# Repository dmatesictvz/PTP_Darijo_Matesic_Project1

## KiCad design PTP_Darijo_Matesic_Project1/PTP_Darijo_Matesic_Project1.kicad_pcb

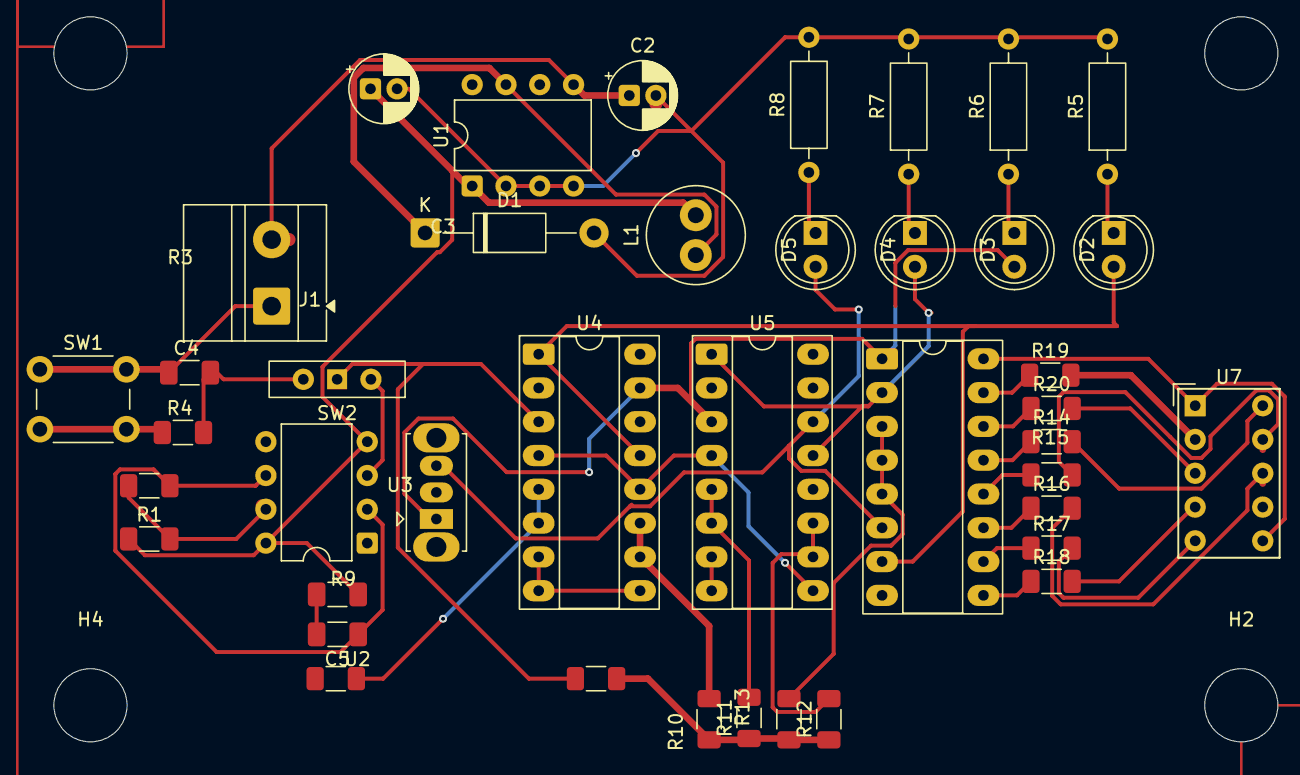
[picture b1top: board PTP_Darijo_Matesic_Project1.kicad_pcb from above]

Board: 2 copper layers, 45 parts (0 on the bottom side), 38 nets.

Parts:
C1: 220u; CP_Radial_D5.0mm_P2.00mm
C2: 22u; CP_Radial_D5.0mm_P2.00mm
C3: 100n; C_1206_3216Metric_Pad1.33x1.80mm_HandSolder
C4: 1u; C_1206_3216Metric_Pad1.33x1.80mm_HandSolder
C5: 10u; C_1206_3216Metric_Pad1.33x1.80mm_HandSolder
D1: 11DQ06; D_DO-41_SOD81_P12.70mm_Horizontal
D2, D3, D4, D5: LED; LED_D5.0mm
H1, H2, H3, H4: MountingHole; MountingHole_5.5mm
J1: Screw_Terminal_01x02; TerminalBlock_MetzConnect_Type011_RT05502HBLC_1x02_P5.00mm_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
L1: 330u; L_Radial_D7.2mm_P3.00mm_Murata_1700
R1, R2: 47k; R_1206_3216Metric_Pad1.30x1.75mm_HandSolder
R3, R9, R10, R11, R12: 10k; R_1206_3216Metric_Pad1.30x1.75mm_HandSolder
R4, R14, R15, R16, R17, R18, R19, R20: 2k; R_1206_3216Metric_Pad1.30x1.75mm_HandSolder
R5, R6, R7, R8: 4K7; R_Axial_DIN0207_L6.3mm_D2.5mm_P10.16mm_Horizontal
R13: R; R_1206_3216Metric_Pad1.30x1.75mm_HandSolder
SW1: SW_Push; SW_PUSH_6mm_H4.3mm
SW2: SW_Wuerth_450301014042; SW_Slide-03_Wuerth-WS-SLTV_10x2.5x6.4_P2.54mm
U1: LM2574N-5; DIP-8_W7.62mm
U2: NE555P; DIP-8_W7.62mm
U3: SN74LVC1G11; SW_Slide_SPDT_Straight_CK_OS102011MS2Q
U4, U5: 4027; DIP-16_W7.62mm_Socket_LongPads
U6: 74LS47; DIP-16_W7.62mm_Socket_LongPads
U7: FYS-3911BUHR-21; HDSP-7401

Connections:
555: SW2.2 (C), U2.3 (Q)
+5V: C1.1, C3.1, L1.2, R1.1, R3.1, R9.1, R10.1, R11.1, R12.1, R13.1, U1.1 (FB), U2.4 (R), U2.8 (VCC), U4.16 (VDD), U5.16 (VDD), U6.16 (VCC), U7.1 (CA), U7.6 (CA)
CLOCK: R3.2, SW2.1 (B), U4.3 (C)
GND: C1.2, C2.2, C3.2, C4.1, C5.2, D1.2 (A), J1.1, R5.2, R6.2, R7.2, R8.2, SW1.1, U1.2 (SGND), U1.3 (~ON/OFF), U1.4 (PGND), U2.1 (GND), U3.2 (GND), U4.7 (S), U4.8 (VSS), U4.9 (S), U5.7 (S), U5.8 (VSS), U5.12 (R), U6.8 (GND)
unnamed: D1.1 (K), L1.1, U1.7 (OUT)
unnamed: D2.1 (K), R5.1
unnamed: D3.1 (K), R6.1
unnamed: D4.1 (K), R7.1
unnamed: D5.1 (K), R8.1
unnamed: R4.1, SW1.2
unnamed: C4.2, R4.2, SW2.3 (A)
unnamed: R1.2, R2.1, U2.7 (DIS)
unnamed: C5.1, R2.2, U2.2 (TR), U2.6 (THR)
unnamed: R9.2, U4.5 (K), U4.6 (J)
unnamed: R10.2, U4.10 (J), U4.11 (K)
unnamed: R11.2, U5.5 (K), U5.6 (J)
unnamed: R12.2, U5.10 (J), U5.11 (K)
unnamed: R13.2, U6.3 (LT), U6.4 (BI), U6.5 (RBI)
unnamed: R14.1, U6.13 (a)
unnamed: R15.1, U6.12 (b)
unnamed: R16.1, U6.11 (c)
unnamed: R17.1, U6.10 (d)
unnamed: R18.1, U6.9 (e)
unnamed: R19.1, U6.15 (f)
unnamed: R20.1, U6.14 (g)
unnamed: R14.2, U7.10 (A)
unnamed: R15.2, U7.9 (B)
unnamed: R16.2, U7.8 (C)
unnamed: R17.2, U7.5 (D)
unnamed: R18.2, U7.4 (E)
unnamed: R19.2, U7.2 (F)
unnamed: R20.2, U7.3 (G)
Q0: D2.2 (A), U4.1 (Q), U4.13 (C), U6.7 (A)
Q1: D3.2 (A), U3.1 (A), U4.15 (Q), U5.3 (C), U6.1 (B)
Q2: D4.2 (A), U5.1 (Q), U5.13 (C), U6.2 (C)
Q3: D5.2 (A), U3.3 (B), U5.14 (~Q), U6.6 (D)
RESET: U4.4 (R), U4.12 (R), U5.4 (R), U5.9 (S)
VDD: C2.1, J1.2, U1.5 (VIN)

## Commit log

2025-10-22 .
    .
2025-10-29 A
    A
2025-12-03 gt
    t
